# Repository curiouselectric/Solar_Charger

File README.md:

# Solar_Charger
A DIY Solar Charger for 18650 Lithium Ion cells.

Get off-grid, power your remote project and learn about solar power with this DIY solar charger kit.

This is a relatively simple open-source kit, sold at www.curiouselectric.co.uk and on Tindie: https://www.tindie.com/products/reinnovation/solar-matic/, which includes two 1Wp solar PV panels and all the parts required to recharge standard 18650 lithium ion cells.

The charger IC is the [BQ24210 from Texas Instruments](http://www.ti.com/lit/ds/symlink/bq24210.pdf). This is an amazing single-cell Lithium Ion battery charge IC with up to 800mA current rating. It is designed to maximise the output from a solar PV cell into the battery. This is a very small surface mount component in a WSON-10 package, so we have soldered this to the PCB for you.

The kit is uses a DC-DC converter which ensures a regulated 5V output, either for a USB connector output or for screw terminals. The DC-DC converter is controlled via a switch on the side of the PCB.

The unit comes with a simple laser-cut enclosure so it can be placed on a window-sill or hung somewhere.

This is a reasonably simple kit which requires some soldering and a few fiddly connections.

*Note: Depending upon the capacity of the 18650 cell, in the UK the battery will fully recharge in around 3-5 days during an average summers day. This totally depends upon the solar resource available.*

*Note: The enclosure is NOT waterproof or for outdoor use.*

This repository is for all the design files for this project.
This includes:

* PCB design (KiCAD files)
* Enclosure Design (.dxf designs)
* Instructions (open-office and .pdf)

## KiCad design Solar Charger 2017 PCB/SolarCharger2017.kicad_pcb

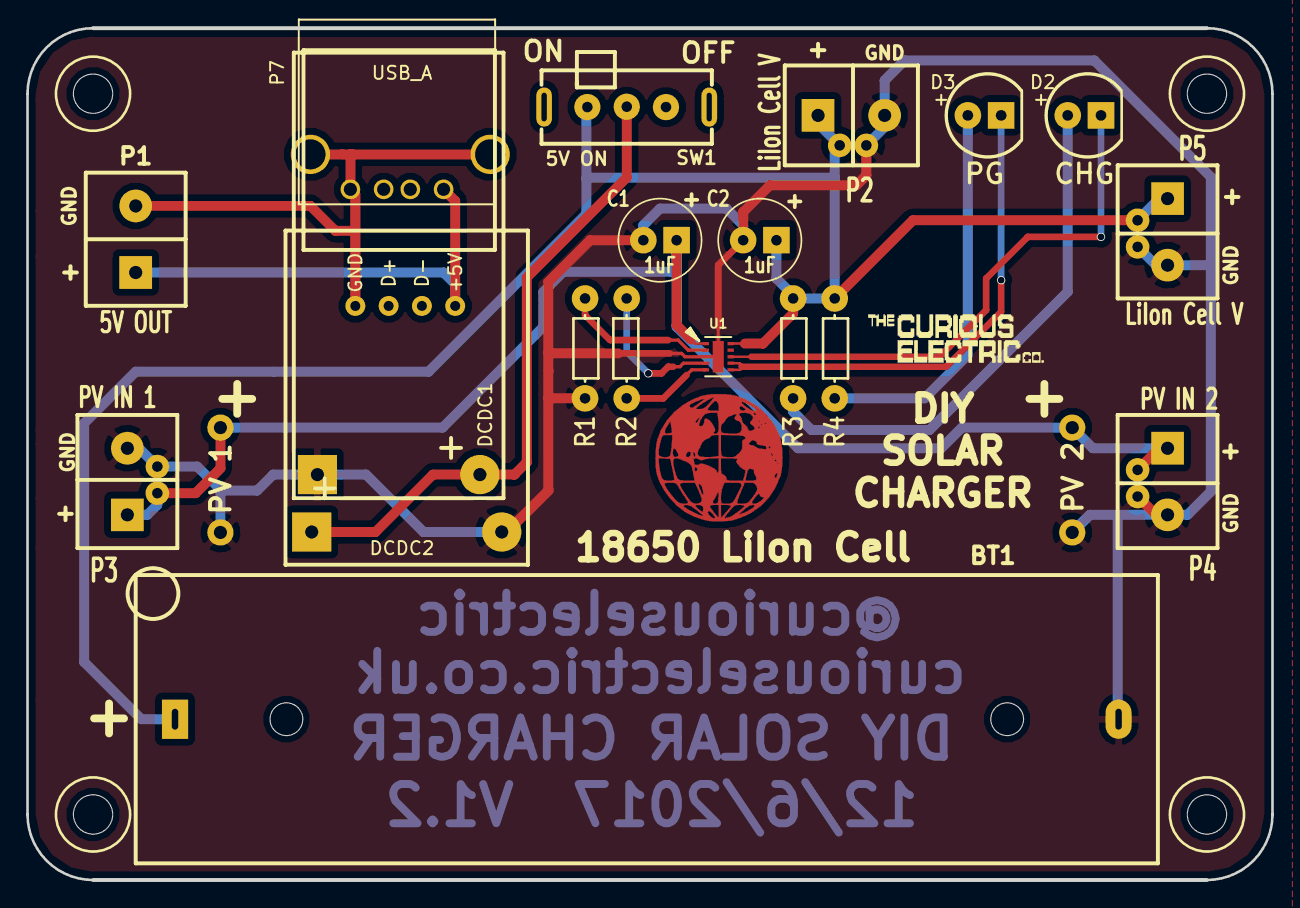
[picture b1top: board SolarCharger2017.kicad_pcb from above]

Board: 2 copper layers, 95.0 x 65.0 mm, 23 parts (0 on the bottom side), 13 nets.

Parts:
BT1: 18650 LiIon Cell; TH_LiIon_Holder
C1, C2: 1uF; C1V7_lg_pad_lg_hole
D2: CHG; TH_LED-5MM_larg_pad
D3: PG; TH_LED-5MM_larg_pad
DCDC1: DC-DC; TH_DCDC_Converter_USB
DCDC2: DC-DC; TH_DCDC_Converter_NoUSB
LG1: LOGO1; CEC_Globe_10mm_FCU
LG2: LOGO2; TCEC_Words_13mm
P1: 5V OUT; SIL-2_screw_terminal
P2, P5: LiIon Cell V; SIL_2_screw_+_JST_2mm
P3: PV IN 1; SIL_2_screw_+_JST_2mm
P4: PV IN 2; SIL_2_screw_+_JST_2mm
P7: USB_A
PCB1: PCB; PCB_65x90mm
R1: 1k; TH_Resistor_1
R2: 100k; TH_Resistor_1
R3, R4: 2.2k; TH_Resistor_1
SC1: PV <2W 5.5V; PV_130mmx65mm_NoOutline
SW1: 5V ON; SW_SPDT_R_Angle_ALIEX
U1: BQ24210; SM_WSON-10-2x3

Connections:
GND: BT1.2, C1.2, C2.2, DCDC1.1, DCDC2.1, P2.2, P3.2, P4.2, P5.2, R1.2, SC1.2, U1.3, U1.PAD
unnamed: C1.1, P3.1, P4.1, SC1.1, U1.1
unnamed: D2.1, U1.8
unnamed: D2.2, R3.2
unnamed: D3.1, U1.6, U1.7
unnamed: D3.2, R4.2
unnamed: DCDC1.2, DCDC2.2, SW1.2
unnamed: DCDC2.3, P1.1, P7.1
unnamed: DCDC2.4, P1.2, P7.4, P7.5
unnamed: R1.1, U1.2
unnamed: R2.1, U1.5
unnamed: R2.2, U1.4
VCC: BT1.1, C2.1, P2.1, P5.1, R3.1, R4.1, SW1.1, U1.10

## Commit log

2017-06-12 Initial comit
2017-06-12 Update of PCB
2017-08-18 Changes to PCB
    DC-DC converter correct. Moved silkscreen. Sorted costs
2017-08-18 Added gerbers
2017-08-18 Update of Gerber
2017-08-18 Slight update of schematic
2017-09-15 Updated PCB
2017-09-15 Added inital instructions
    Instructions to be finished. Not correct yet!
2017-09-24 Updated instructions and parts list
2017-10-07 Updated enclosure
2017-10-26 Added instructions
2017-11-05 Added datasheet
2017-11-17 Update of instructions
2017-11-17 Updated instructions
2017-12-24 Update of PCB with USB output
    Slight change to the USB output.
